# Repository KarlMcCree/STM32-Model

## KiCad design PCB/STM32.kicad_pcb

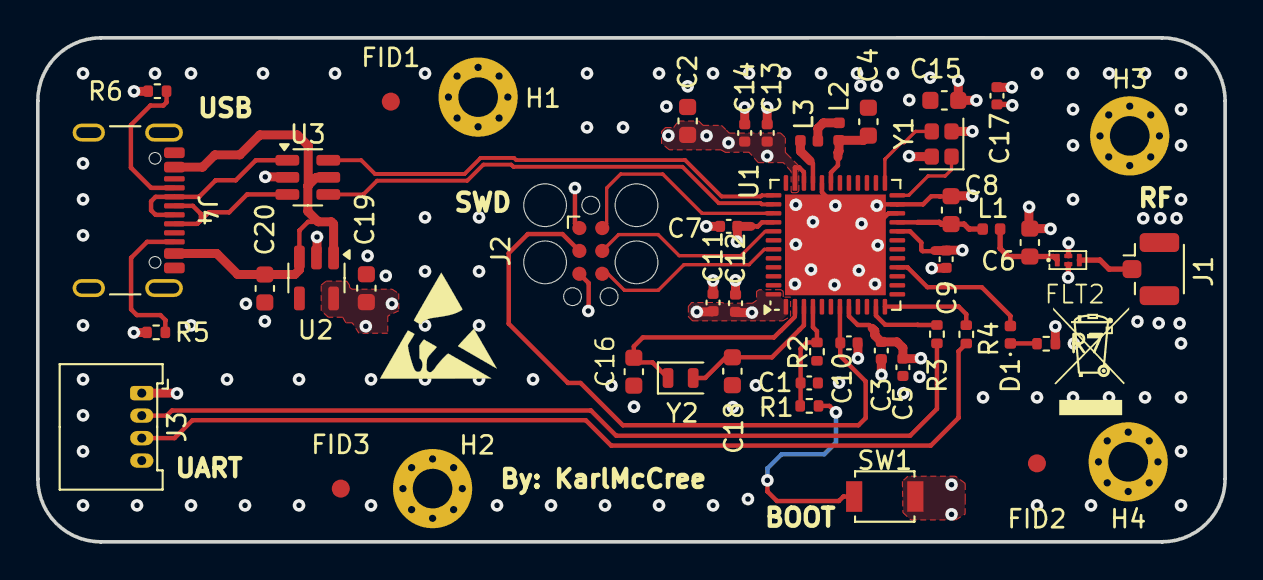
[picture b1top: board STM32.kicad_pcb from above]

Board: 4 copper layers, 66.0 x 28.0 mm, 49 parts (0 on the bottom side), 31 nets.

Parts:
C1, C3, C5, C7, C9, C10, C11, C12, C13, C17: 100u; C_0402_1005Metric
C2, C4, C15, C19, C20: 4u7; C_0603_1608Metric
C6: 0p8; C_0603_1608Metric
C8: 0p3; C_0603_1608Metric
C14: 100p; C_0402_1005Metric
C16, C18: 10p; C_0603_1608Metric
D1: LED; LED_0402_1005Metric
FID1, FID2, FID3: Fiducial; Fiducial_1mm_Mask3mm
FLT2: DLF162500LT-5028A1
H1, H2, H3, H4: MountingHole_Pad; MountingHole_2.2mm_M2_Pad_Via
J1: Conn_Coaxial; U.FL_Hirose_U.FL-R-SMT-1_Vertical
J2: Conn_ARM_SWD_TagConnect_TC2030; Tag-Connect_TC2030-IDC-FP_2x03_P1.27mm_Vertical
J3: Conn_01x04; Molex_PicoBlade_53048-0410_1x04_P1.25mm_Horizontal
J4: USB_C_Receptacle_USB2.0_16P; USB_C_Receptacle_GCT_USB4105-xx-A_16P_TopMnt_Horizontal
L1: 2n7; L_0402_1005Metric
L2, L3: 10n; L_0402_1005Metric
R1: 100n; R_0402_1005Metric
R2: 5K1; R_0402_1005Metric
R3, R4, R7: 220R; R_0402_1005Metric
R5, R6: R; R_0402_1005Metric
SW1: SW_Push; SW_SPST_B3U-1000P
U1: STM32WB55CEUx; QFN-48-1EP_7x7mm_P0.5mm_EP5.6x5.6mm
U2: MIC5365-3.3YD5; TSOT-23-5
U3: USBLC6-2SC6; SOT-23-6
Y1: 38MHz; Crystal_SMD_2016-4Pin_2.0x1.6mm
Y2: 32Hz768; Crystal_SMD_2012-2Pin_2.0x1.2mm

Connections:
+3V3: C2.1, C3.1, C5.1, C7.1, C9.1, C11.1, C12.1, C13.1, C14.1, C15.1, C17.1, C19.1, J2.1 (VCC), J3.1, SW1.1, U1.1 (VBAT), U1.8 (VDDA), U1.20 (VDD), U1.34 (VDDSMPS), U1.35 (VDD), U1.40 (VDDUSB), U1.48 (VDD), U2.5 (VOUT)
+5V: C20.1, J4.A4 (VBUS), J4.A9 (VBUS), J4.B4 (VBUS), J4.B9 (VBUS), U2.1 (VIN), U2.3 (EN), U3.5 (VBUS)
/BOOT0: C1.1, R1.2, R2.1, U1.4 (PH3)
/HSE_IN: U1.25 (OSC_IN), Y1.3
/HSE_OUT: U1.24 (OSC_OUT), Y1.1
/LSE_IN: C16.1, U1.2 (PC14), Y2.1
/LSE_OUT: C18.1, U1.3 (PC15), Y2.2
/RF: C8.1, L1.2, U1.21 (RF1)
/RF-ANT: FLT2.3 (OUT), J1.1 (In)
/RF-MATCH: C6.1, FLT2.1 (IN), L1.1
/SMP: L2.2, L3.1
/SMPSFB: C4.1, L2.1, U1.31 (VFBSMPS)
/SMPSLX: L3.2, U1.33 (VLXSMPS)
/SWD_CLK: J2.4 (SWCLK), U1.41 (PA14)
/SWD_DIO: J2.2 (SWDIO), U1.39 (PA13)
/SWD_NRST: C10.1, J2.3 (~RESET), U1.7 (NRST)
/SWD_TRC: J2.6 (SWO), U1.43 (PB3)
/UART_RX: R4.1, U1.12 (PA3)
/UART_RXC: J3.3, R4.2
/UART_TX: R3.1, U1.11 (PA2)
/UART_TXC: J3.2, R3.2
/USB_+D: J4.A6 (D+), J4.B6 (D+), U3.3 (I/O2)
/USB_-D: J4.A7 (D-), J4.B7 (D-), U3.1 (I/O1)
/USB_C1: J4.A5 (CC1), R6.1
/USB_C2: J4.B5 (CC2), R5.1
/USB_D+: U1.38 (PA12), U3.4 (I/O2)
/USB_D-: U1.37 (PA11), U3.6 (I/O1)
GND: C1.2, C2.2, C3.2, C4.2, C5.2, C6.2, C7.2, C8.2, C9.2, C10.2, C11.2, C12.2, C13.2, C14.2, C15.2, C16.2, C17.2, C18.2, C19.2, C20.2, FLT2.2 (GND), FLT2.4 (GND), H1.1, H2.1, H3.1, H4.1, J1.2 (Ext), J2.5 (GND), J3.4, J4.A1 (GND), J4.A12 (GND), J4.B1 (GND), J4.B12 (GND), J4.S1 (SHIELD), R2.2, R5.2, R6.2, R7.2, U1.22 (VSSRF), U1.23 (VDDRF), U1.32 (VSSSMPS), U1.49 (VSS), U2.2 (GND), U3.2 (GND), Y1.2, Y1.4
unnamed: D1.2 (A), U1.16 (PA7)
unnamed: D1.1 (K), R7.1
unnamed: R1.1, SW1.2
